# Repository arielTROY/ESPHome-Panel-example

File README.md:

# AI Wearable PCB - Atopile Design

## Overview

This project implements an ultra-compact AI wearable PCB designed using the [Atopile](https://atopile.io) framework. The design targets a 28mm × 28mm form factor with comprehensive AI capabilities including camera, microphone, speaker, and cellular connectivity.

## Features

- **ESP32-S3 Brain**: WiFi, BLE, camera interface, I2S audio
- **OV2640 Camera**: 2MP sensor with high FOV
- **SPH0645LM4H MEMS Microphone**: Always-on recording capability
- **MAX98357A Audio Amplifier**: Clear AI response playback
- **SIM7070G Cellular Module**: Global eSIM connectivity
- **BQ25185 + TPS63001 Power Management**: Efficient battery charging and regulation
- **500mAh LiPo Battery**: 28+ hour battery life
- **USB Type-C**: Charging and programming interface

## Project Structure

```
.
├── main.ato                    # Original full design
├── ai_wearable_final.ato      # Simplified version that builds successfully
├── power_management.ato        # Battery charging and power regulation
├── audio_system.ato           # Audio recording and playback
├── camera_interface.ato       # Camera module interface
├── cellular_module.ato        # eSIM cellular connectivity
├── esp32_s3.ato              # ESP32-S3 module definition
├── generics/                  # Generic component definitions
│   ├── resistors.ato
│   ├── capacitors.ato
│   └── inductors.ato
├── layouts/                   # Generated KiCad files
│   └── default/
│       ├── default.kicad_pcb
│       ├── default.kicad_pro
│       └── fp-lib-table
├── component-selection.md     # Detailed component analysis
├── project_summary.md         # Project overview and results
└── ato.yaml                  # Atopile project configuration
```

## Building the Project

### Prerequisites

1. Install Atopile:
```bash
pip install atopile
```

2. Install dependencies:
```bash
cd ai-wearable/my_first_ato_project
atopile install
```

### Build Commands

Build the PCB design:
```bash
python3 -m atopile build
```

This generates:
- KiCad PCB layout files in `layouts/default/`
- Bill of Materials in `build/builds/default/default.bom.csv`

## Design Specifications

- **PCB Size**: 28mm × 28mm (4-layer)
- **Power Consumption**: ~17.6mA average
- **Battery Life**: 28+ hours (500mAh battery)
- **Development**: Arduino IDE compatible (ESP32-S3)
- **Manufacturing**: JLCPCB ready with LCSC part numbers

## Key Components

| Component | Part Number | Description |
|-----------|-------------|-------------|
| ESP32-S3-WROOM-1 | C2913202 | Main processor |
| OV2640 | C2839795 | 2MP camera module |
| SPH0645LM4H | C2688116 | I2S MEMS microphone |
| MAX98357A | C2684264 | I2S audio amplifier |
| SIM7070G | C2830486 | Global cellular module |
| BQ25185 | C2837321 | Battery charger |
| TPS63001 | C88313 | Buck-boost converter |

## Next Steps

1. **PCB Layout**: Open `layouts/default/default.kicad_pcb` in KiCad
2. **Component Placement**: Optimize for 28mm × 28mm target
3. **Routing**: Complete 4-layer PCB routing
4. **Manufacturing**: Export Gerbers and order from JLCPCB

## Documentation

- [Component Selection Analysis](component-selection.md)
- [Project Summary](project_summary.md)
- [Atopile Documentation](https://docs.atopile.io)

## License

This project is open source. Feel free to use and modify for your own AI wearable designs.

## Contributing

Contributions are welcome! Please feel free to submit issues or pull requests.

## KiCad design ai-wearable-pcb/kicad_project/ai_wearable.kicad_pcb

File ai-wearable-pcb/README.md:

# AI Wearable Dev Board (30mm × 30mm)

This is an ultra-compact AI wearable development board designed for smart glasses, body cameras, and other wearable AI applications.

## Features

### Main Components

1. **MCU**: ESP32-S3-MINI-1 (LCSC: C2980299)
   - Dual-core Xtensa LX7 @ 240MHz
   - Wi-Fi 802.11 b/g/n
   - Bluetooth 5.0 (LE)
   - Camera interface support
   - AI acceleration capabilities

2. **Cellular Module**: SIM7080G (LCSC: C2943992)
   - LTE Cat-M1/NB-IoT
   - eSIM support via Nano SIM holder
   - Global band support
   - Low power consumption

3. **Camera**: OV2640
   - 2MP resolution
   - Wide FOV lens
   - Privacy LED indicator (red)
   - I2C control interface

4. **Audio**:
   - PDM Digital MEMS Microphone
   - MAX98357A I2S Audio Amplifier
   - 8Ω Speaker support
   - Recording LED indicator (orange)

5. **Power Management**:
   - USB-C connector with proper CC resistors (5.1kΩ)
   - BQ24074 LiPo battery charger (or similar)
   - TPS62840 ultra-low Iq buck regulator (3.3V)
   - BQ27441 fuel gauge
   - 400-600mAh LiPo battery support
   - NTC thermistor for battery temperature monitoring

6. **User Interface**:
   - Large "Query" button (6×6mm)
   - Reset button (3×3mm)
   - Boot button (3×3mm)
   - Slide power switch
   - Status LEDs:
     - Red: 5V USB power present
     - Green: 3.3V rail active
     - Blue: GPIO-controlled status
     - Orange: Recording active
     - Red: Camera privacy indicator

7. **Connectivity**:
   - USB-C for charging and data
   - QWIIC/I2C connector (JST-SH 4-pin)
   - Chip antenna for cellular

## Board Specifications

- **Size**: 30mm × 30mm (4-layer PCB recommended)
- **Component Size**: 0603 for all passive components
- **Power Input**: 5V via USB-C
- **Battery Voltage**: 3.7V nominal (LiPo)
- **System Voltage**: 3.3V
- **Current Consumption**: 
  - Sleep: <1mA
  - Active: ~200-500mA (depending on cellular/camera usage)

## Pin Connections

### ESP32-S3 Key Connections:
- **USB**: D+ and D- connected to USB-C with proper routing
- **Camera**: DVP interface (8-bit data + control signals)
- **Audio**: I2S interface to MAX98357A
- **Microphone**: PDM interface
- **Cellular**: UART interface to SIM7080G
- **I2C**: Shared bus for camera control, fuel gauge, and QWIIC connector
- **GPIO**: Status LEDs, button inputs, enable signals

### Protection Features:
- ESD protection on USB data lines
- RC circuits on MCU EN/RESET pins
- Proper bypass capacitors on all power rails
- Pull-up resistors on I2C bus (4.7kΩ)

## Assembly Notes

1. Place all 0603 components first
2. Ensure proper orientation of polarized components (LEDs, capacitors)
3. USB-C connector requires careful soldering
4. Battery should be mounted on the back of the PCB
5. Speaker can be connected via wire leads or pogo pins

## Software Support

The board is compatible with:
- Arduino IDE (ESP32 board package)
- ESP-IDF
- MicroPython
- CircuitPython

## Safety Considerations

- Battery charging is temperature monitored via NTC
- Overcurrent protection in charger IC
- Thermal regulation in buck converter
- Short-circuit protection on all outputs

## Applications

- Smart glasses
- Body cameras
- Health monitoring devices
- Asset tracking
- Environmental sensing
- AI-powered wearables
- Solar-powered devices (with appropriate input protection)

## LCSC Part Numbers Summary

- ESP32-S3-MINI-1: C2980299
- SIM7080G: C2943992
- BQ27441 (Fuel Gauge): C139621
- Nano SIM Holder: C2895022
- 0603 Resistors: Various values
- 0603 Capacitors: Various values
- LEDs (0603): Red, Green, Blue, Orange

## Design Files

- `main.ato`: Atopile hardware description
- `ato.yaml`: Project configuration
- Build outputs in `build/` directory

## Building

To build the project:
```bash
python3 -m atopile build
```

## License

This project is open source hardware. Feel free to modify and use for your projects.

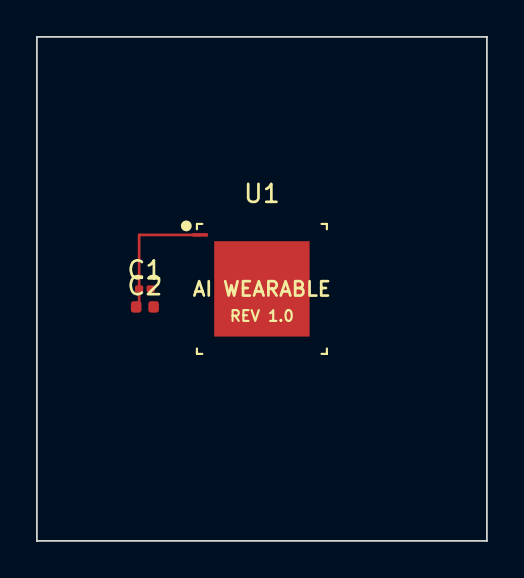
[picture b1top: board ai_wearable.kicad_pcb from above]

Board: 4 copper layers, 25.0 x 28.0 mm, 3 parts (0 on the bottom side), 2 nets.

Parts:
C1: 100nF; C_0201_0603Metric
C2: 4.7uF; C_0402_1005Metric
U1: nRF52840; Nordic_AQFN-73-1EP_7x7mm_P0.5mm

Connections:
+3V3: C1.1, C2.1, U1.1
GND: C1.2, C2.2, U1.74

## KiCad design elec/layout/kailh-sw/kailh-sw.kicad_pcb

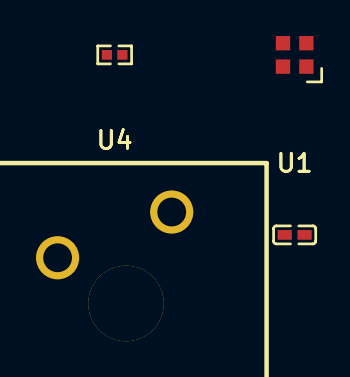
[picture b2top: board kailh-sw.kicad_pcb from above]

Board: 2 copper layers, 4 parts (0 on the bottom side), 3 nets, no tracks yet.

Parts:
U1: 100nF ±10% 16V X7R; C0402-b3ef17
U2: LED-SMD_4P-L2.0-W2.0-BR
U3: 10kΩ ±1% 62.5mW; R0402-56259e
U4: KEY-TH_CPG1511F01S0X

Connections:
KEY: U3.2, U4.1
gnd: U1.2, U2.3, U4.2
hv: U1.1, U2.1, U3.1

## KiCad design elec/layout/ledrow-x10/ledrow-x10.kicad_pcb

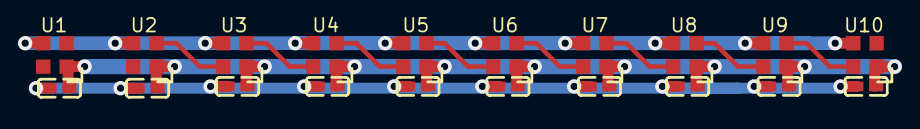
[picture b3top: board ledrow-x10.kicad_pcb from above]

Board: 2 copper layers, 20 parts (0 on the bottom side), 11 nets.

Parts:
C1, C2, C3, C4, C5, C6, C7, C8, C9, C10: 100nF ±10% 16V X7R; C0402-b3ef17
U1, U2, U3, U4, U5, U6, U7, U8, U9, U10: LED-SMD_4P-L2.0-W2.0-BR

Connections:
gnd: C1.2, C2.2, C3.2, C4.2, C5.2, C6.2, C7.2, C8.2, C9.2, C10.2, U1.3, U2.3, U3.3, U4.3, U5.3, U6.3, U7.3, U8.3, U9.3, U10.3
hv: C1.1, C2.1, C3.1, C4.1, C5.1, C6.1, C7.1, C8.1, C9.1, C10.1, U1.1, U2.1, U3.1, U4.1, U5.1, U6.1, U7.1, U8.1, U9.1, U10.1
io: U2.2, U3.4
io-1: U6.2, U7.4
io-2: U9.2, U10.4
io-3: U5.2, U6.4
io-4: U1.2, U2.4
vcc: U3.2, U4.4
vcc-1: U7.2, U8.4
vcc-2: U4.2, U5.4
vcc-3: U8.2, U9.4

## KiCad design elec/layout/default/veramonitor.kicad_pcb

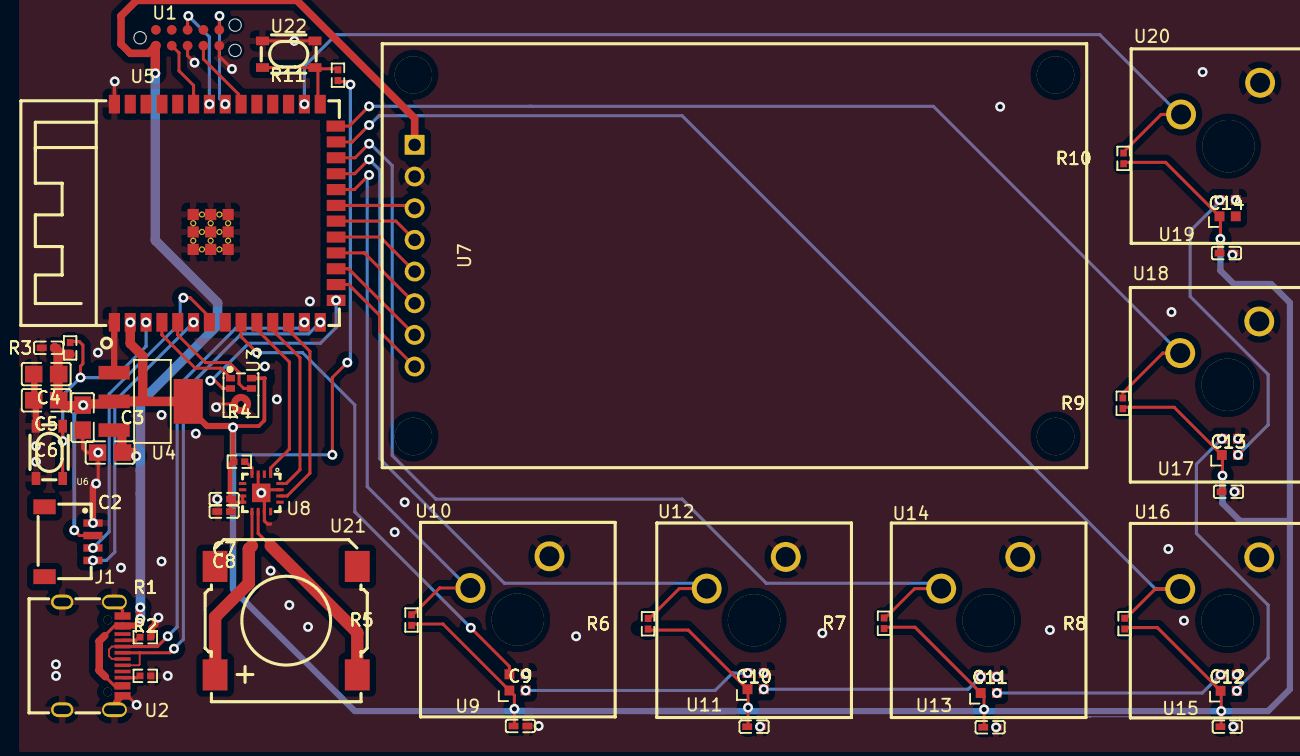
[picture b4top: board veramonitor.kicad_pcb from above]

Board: 2 copper layers, 47 parts (0 on the bottom side), 44 nets.

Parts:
C2, C3, C5, C6: 10µF ±10% 25V X5R; C0805-3b2e55
C4, C8, C9, C10, C11, C12, C13, C14: 100nF ±10% 16V X7R; C0402-b3ef17
C7: 10µF ±20% 10V X5R; C0402-b3ef17
J1: CONN-SMD_4P-P1.00_SM04B-SRSS-TB-LF-SN
R1, R2: 4.7kΩ ±1% 62.5mW; R0402-56259e
R3, R4, R5, R6, R7, R8, R9, R10, R11: 10kΩ ±1% 62.5mW; R0402-56259e
U1: TAG-CONNECT_TC2050-IDC
U2: USB-C-SMD_KH-TYPE-C-16P
U3: MIC-SMD_5P_L3.5-W2.7-P0.82_SPH0641LU4H-1
U4: SOT-223-3_L6.5-W3.4-P2.30-LS7.0-BR
U5: WIRELM-SMD_ESP32-S3-WROOM-1
U6, U22: KEY-SMD_4P-L4.2-W3.2-P2.20-LS4.6
U7: LCD-TH_L56.5-W34.0_1-8INCH-LCD-MODULE
U8: TQFN-16_L3.0-W3.0-P0.50-BL-EP1.5
U9, U11, U13, U15, U17, U19: LED-SMD_4P-L2.0-W2.0-BR
U10, U12, U14, U16, U18, U20: KEY-TH_CPG1511F01S0X
U21: BUZ-SMD_4P-L13.0-W13.0-P11.4-BL

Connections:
B5: R2.1, U2.B5
BCLK: U5.11, U8.16
BL: U5.16, U7.8
CC1: R1.1, U2.A5
DIN: U5.10, U8.1
DIN-1: U5.9, U9.4
DUMMY: U21.3, U21.4
KEY: R10.2, U5.28, U20.1
KEY-1: R5.2, U5.22, U10.1
KEY-2: R6.2, U5.23, U12.1
KEY-3: R8.2, U5.25, U16.1
KEY-4: R9.2, U5.26, U18.1
KEY-5: R7.2, U5.24, U14.1
LRCLK: U5.12, U8.14
N_period_C_period: U8.5, U8.6, U8.12, U8.13
OUTN: U8.10, U21.2
OUTP: U8.9, U21.1
RST: U5.17, U7.7
SD_MODE_hash: R4.2, U8.4
cs: U5.18, U7.6
dm: U2.A7, U2.B7, U5.13
dp: U2.A6, U2.B6, U5.14
gnd: C2.2, C3.2, C4.2, C5.2, C6.2, C7.2, C8.2, C9.2, C10.2, C11.2, C12.2, C13.2, C14.2, J1.1, R1.2, R2.2, U1.3, U1.5, U2.1, U2.2, U2.3, U2.4, U2.A1, U2.A12, U2.B1, U2.B12, U3.3, U4.1, U5.1, U5.40, U5.41, U6.3, U6.4, U7.2, U8.3, U8.11, U8.15, U8.17, U9.3, U10.2, U11.3, U12.2, U13.3, U14.2, U15.3, U16.2, U17.3, U18.2, U19.3, U20.2, U22.3, U22.4
hv: C3.1, C4.1, C5.1, C6.1, C7.1, C8.1, C9.1, C10.1, C11.1, C12.1, C13.1, C14.1, J1.2, R3.1, R4.1, R5.1, R6.1, R7.1, R8.1, R9.1, R10.1, R11.1, U3.5, U4.2, U4.4, U5.2, U8.7, U8.8, U9.1, U11.1, U13.1, U15.1, U17.1, U19.1
hv-1: C2.1, U1.1, U2.A4, U2.A9, U2.B4, U2.B9, U4.3, U7.1
in: R3.2, U5.3, U6.1, U6.2
in-1: R11.2, U5.27, U22.1, U22.2
io: U9.2, U11.4
io-1: U13.2, U15.4
io-2: U15.2, U17.4
miso: U5.21, U7.3
mosi: U5.19, U7.5
pdm_clk: U3.4, U5.5
pdm_data: U3.1, U5.4
pdm_sel: U3.2, U5.15
sck: U5.20, U7.4
scl: J1.4, U5.6
sda: J1.3, U5.7
tck: U1.4, U5.32
tdi: U1.8, U5.34
tdo: U1.6, U5.33
tms: U1.2, U5.35
vcc: U11.2, U13.4
vcc-1: U17.2, U19.4

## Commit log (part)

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2025-04-12 fixing
2025-04-12 build with v3
2025-07-25 Initialize AI wearable project with Atopile design files and CI workflow
2025-07-25 Create AI wearable PCB project with ultra-compact design files
2025-07-25 Update GitHub Actions artifact upload to v4 across multiple workflows
2025-07-25 Update ato.yaml files to use requires-atopile instead of ato-version
2025-07-25 Update ato.yaml to version 0.10.0 and restructure project configuration
2025-07-25 Update GitHub Actions artifact upload to v4
2025-07-25 Update ATO version declaration syntax in configuration file
2025-07-25 Refactor ato.yaml: Move builds and dependencies to top-level
2025-07-25 Refactor dependencies in ato.yaml to use simplified list syntax
2025-07-25 Simplify dependencies syntax in ato.yaml
2025-07-25 Add manual fix instructions for Faebryk InvalidPackageIdentifierError
2025-07-25 Add troubleshooting guide and update CI workflow image tag
2025-07-25 Add fix script for atopile/faebryk package errors
2025-07-25 Add CI workflow and bug report for atopile dependency issues
2025-07-25 Update CI workflow to use python -m atopile for commands
2025-07-25 Refactor CI workflow to use atopile-kicad Docker image and improve build logging
2025-07-25 Add GitHub Actions workflow for AI-Wearable PCB builds
2025-07-25 Add workflow_dispatch trigger to CI workflow
2025-07-25 Add manual workflow dispatch trigger to AI wearable build workflow
2025-07-25 Add ATO_CI env var to disable first-run wizard in CI workflows
2025-07-25 Disable ATO first-run wizard in CI workflow
2025-07-25 Add CI workflow fixes for atopile telemetry and error handling
2025-07-25 Fix telemetry and dependencies inline patch in CI workflow
2025-07-25 Fix atopile build errors with comprehensive error handling and fixes
2025-07-25 Add CI workflows with comprehensive fixes for atopile build issues
2025-07-25 Fix telemetry import and yaml.dump issues in CI workflow
2025-07-25 Simplify CI workflow by removing runtime patching and error handling
2025-07-25 Add sitecustomize to handle dataclass YAML serialization in CI
2025-07-25 Set PYTHONPATH in CI to ensure correct module importing
2025-07-25 Add docker fix script and CI workflow for robust Atopile builds
2025-07-25 Add GitHub Actions workflows for PCB build and export
2025-07-25 Add CI workflows and config to streamline atopile build process
2025-07-25 Checkpoint before follow-up message
2025-07-25 Add fixed GitHub Actions workflow for atopile builds
    - Use Docker container with pre-configured environment
    - Apply necessary fixes for atopile/faebryk issues
    - Handle missing dependencies in subdirectories
    - Add verbose logging for better debugging
    - Continue building other projects even if one fails
    - Capture more artifacts including logs
2025-07-25 Update subproject commit reference
2025-07-25 Add GitHub workflow for debugging Atopile build process
2025-07-25 Create simple LED project with resistor and capacitor
2025-07-25 Remove unnecessary metadata from ato.yaml
2025-07-25 Refactor project structure, update README, and add GitHub upload guide
2025-07-25 Refactor AI wearable board design with ESP32-S3 and comprehensive features
